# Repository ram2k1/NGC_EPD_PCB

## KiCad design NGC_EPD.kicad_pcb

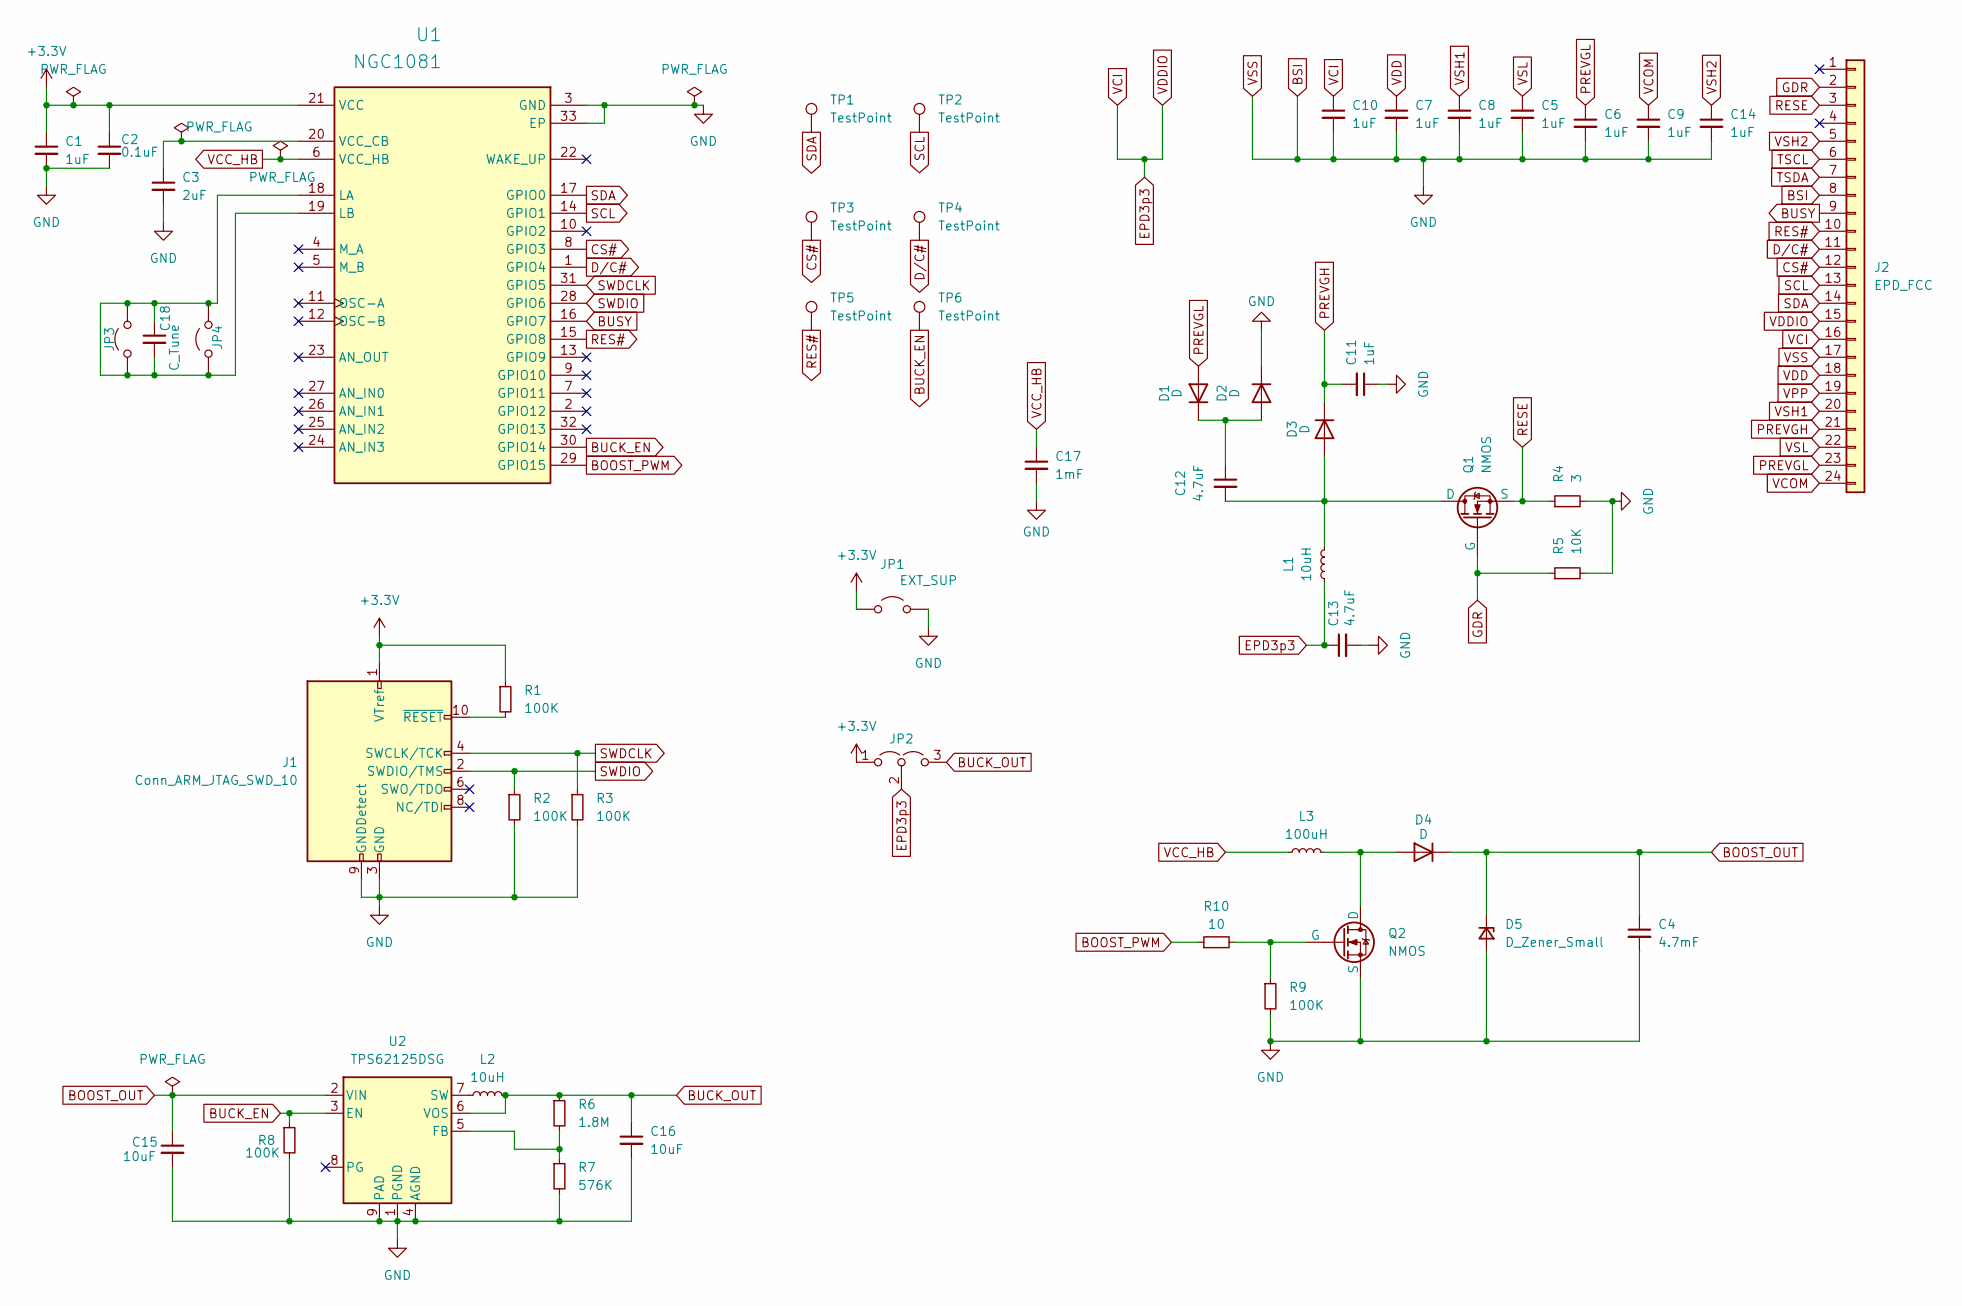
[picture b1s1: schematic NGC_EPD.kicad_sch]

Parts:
C1, C5, C6, C7, C8, C9, C10, C11, C14: 1uF; C_0603_1608Metric_Pad1.08x0.95mm_HandSolder
C2: 0.1uF; C_0402_1005Metric_Pad0.74x0.62mm_HandSolder
C3: 2uF; C_0603_1608Metric_Pad1.08x0.95mm_HandSolder
C4: 4.7mF; CAP_PK&slash_PZ_12P5X25_LOW_RUB
C12, C13: 4.7uF; C_0603_1608Metric_Pad1.08x0.95mm_HandSolder
C15, C16: 10uF; C_0603_1608Metric_Pad1.08x0.95mm_HandSolder
C17: 1mF; 1mF_Nichicon UVR0J102MPD
C18: C_Tune; C_0603_1608Metric_Pad1.08x0.95mm_HandSolder
D1, D2, D3, D4: D; D_SOD-123
D5: D_Zener_Small; D_SOD-123
J1: Conn_ARM_JTAG_SWD_10; PinHeader_2x05_P1.27mm_Vertical_SMD
J2: EPD_FCC; TE_2-1734839-4_1x24-1MP_P0.5mm_Horizontal
JP1, JP3, JP4: EXT_SUP; PinHeader_1x02_P2.54mm_Vertical
JP2: Jumper_3_Open; PinHeader_1x03_P2.54mm_Vertical
L1, L2: 10uH; L_0603_1608Metric_Pad1.05x0.95mm_HandSolder
L3: 100uH; L_0805_2012Metric_Pad1.05x1.20mm_HandSolder
Q1, Q2: NMOS; TSOT-23_HandSoldering
R1, R2, R3, R8, R9: 100K; R_0603_1608Metric_Pad0.98x0.95mm_HandSolder
R4: 3; R_0402_1005Metric_Pad0.72x0.64mm_HandSolder
R5: 10K; R_0603_1608Metric_Pad0.98x0.95mm_HandSolder
R6: 1.8M; R_0805_2012Metric_Pad1.20x1.40mm_HandSolder
R7: 576K; R_0603_1608Metric_Pad0.98x0.95mm_HandSolder
R10: 10; R_0402_1005Metric_Pad0.72x0.64mm_HandSolder
TP1, TP2, TP3, TP4, TP5, TP6: TestPoint; PinHeader_1x01_P1.00mm_Vertical
U1: NGC1081; NGC1081-32QFN
U2: TPS62125DSG; WSON-8-1EP_2x2mm_P0.5mm_EP0.9x1.6mm

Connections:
+3.3V: C1.1, C2.1, J1.1 (VTref), JP1.1 (A), JP2.1 (A), R1.1, U1.21 (VCC)
BOOST_OUT: C4.1, C15.1, D4.1 (K), D5.1 (K), U2.2 (VIN)
BOOST_PWM: R10.1, U1.29 (GPIO15)
BUCK_EN: R8.1, TP6.1, U1.30 (GPIO14), U2.3 (EN)
BUCK_OUT: C16.1, JP2.3 (B), L2.2, R6.1, U2.6 (VOS)
BUSY: J2.9, U1.16 (GPIO7)
CS#: J2.12, TP3.1, U1.8 (GPIO3)
D/C#: J2.11, TP4.1, U1.1 (GPIO4)
EPD3p3: C10.1, C13.1, J2.15, J2.16, JP2.2 (C), L1.1
GDR: J2.2, Q1.2 (G), R5.1
GND: C1.2, C2.2, C3.2, C4.2, C5.2, C6.2, C7.2, C8.2, C9.2, C10.2, C11.1, C13.2, C14.2, C15.2, C16.2, C17.2, D2.1 (K), D5.2 (A), J1.3 (GND), J1.5 (GND), J1.9 (GNDDetect), J2.8, J2.17, JP1.2 (B), Q2.3 (S), R2.2, R3.2, R4.2, R5.2, R7.2, R8.2, R9.2, U1.3 (GND), U1.33 (EP), U2.1 (PGND), U2.4 (AGND), U2.9 (PAD)
unnamed: C12.1, D1.1 (K), D2.2 (A)
unnamed: C12.2, D3.2 (A), L1.2, Q1.1 (D)
unnamed: D4.2 (A), L3.2, Q2.1 (D)
unnamed: J1.10 (~RESET), R1.2
unnamed: C18.1, C18.2, JP3.1 (A), JP3.2 (B), JP4.1 (A), JP4.2 (B), U1.18 (LA), U1.19 (LB)
unnamed: Q2.2 (G), R9.1, R10.2
unnamed: C3.1, U1.20 (VCC_CB)
unnamed: R6.2, R7.1, U2.5 (FB)
unnamed: L2.1, U2.7 (SW)
PREVGH: C11.2, D3.1 (K), J2.21
PREVGL: C6.1, D1.2 (A), J2.23
RES#: J2.10, TP5.1, U1.15 (GPIO8)
RESE: J2.3, Q1.3 (S), R4.1
SCL: J2.13, TP2.1, U1.14 (GPIO1)
SDA: J2.14, TP1.1, U1.17 (GPIO0)
SWDCLK: J1.4 (SWCLK/TCK), R3.1, U1.31 (GPIO5)
SWDIO: J1.2 (SWDIO/TMS), R2.1, U1.28 (GPIO6)
TSCL: J2.6
TSDA: J2.7
VCC_HB: C17.1, L3.1, U1.6 (VCC_HB)
VCOM: C9.1, J2.24
VDD: C7.1, J2.18
VPP: J2.19
VSH1: C8.1, J2.20
VSH2: C14.1, J2.5
VSL: C5.1, J2.22

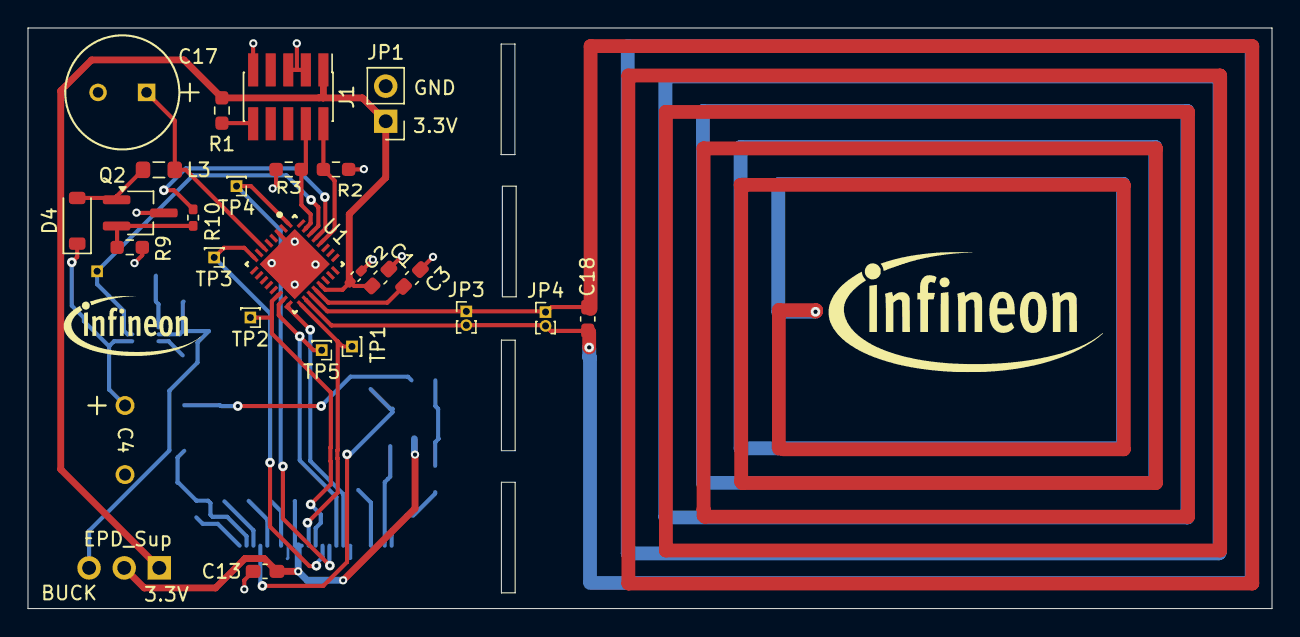
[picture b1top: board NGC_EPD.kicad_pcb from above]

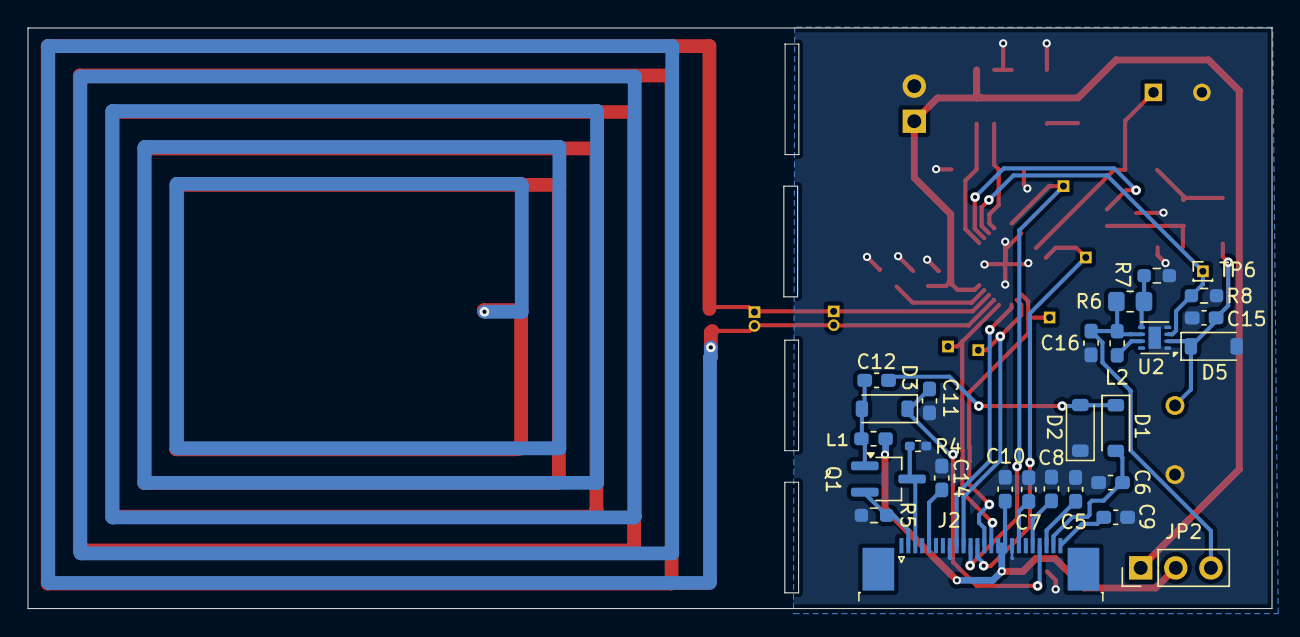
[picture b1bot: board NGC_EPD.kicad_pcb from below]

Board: 2 copper layers, 90.0 x 42.0 mm, 52 parts (27 on the bottom side), 34 nets.

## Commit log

2025-02-06 Initial commit.
    Boost circuit, Antenna, Footprint assignment pending
2025-02-06 Added boost,assigned footprints. Antenna pending
2025-02-08 Finished layout. Seperate antena board required.
2025-02-08 Resolved PCD DRC errors. Added custom antenna. Need tuning of antenna.
2025-02-17 Changed EPD FCC to backside. Added Testpoints and Infineon logo.
2025-02-21 Complete fresh layout. Grouped a functional block components. Placed all the required test points and changed sizes of components (mostly to 0603). Created a single board including antenna(snapable).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
2025-02-22 Routing complete.Added logo.DRC zero errors. Readjusted antenna routing. Added dimensions in user comments layer.
2025-02-22 Routing complete.Added logo.DRC zero errors. (#1)
    Readjusted antenna routing. Added dimensions in user comments layer.
